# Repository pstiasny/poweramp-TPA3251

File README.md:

TPA3251-based power amplifier, 2x150W
=====================================

* [View schematic in KiCanvas](https://kicanvas.org/?github=https%3A%2F%2Fgithub.com%2Fpstiasny%2Fpoweramp-TPA3251%2Fblob%2Fmain%2Famp.kicad_sch)
* [View board in KiCanvas](https://kicanvas.org/?github=https%3A%2F%2Fgithub.com%2Fpstiasny%2Fpoweramp-TPA3251%2Fblob%2Fmain%2Famp.kicad_pcb)

## Notes

*  Amplifier chip is placed on the bottom side.  That design allows for thermal coupling to chassis.
*  I had the board bend a little.  Might be better balanced without the bottom layer ground plane.
*  DC relative to power ground will be present on the ouput terminals.  Add AC coupling capacitors
   in series if that is undesired.

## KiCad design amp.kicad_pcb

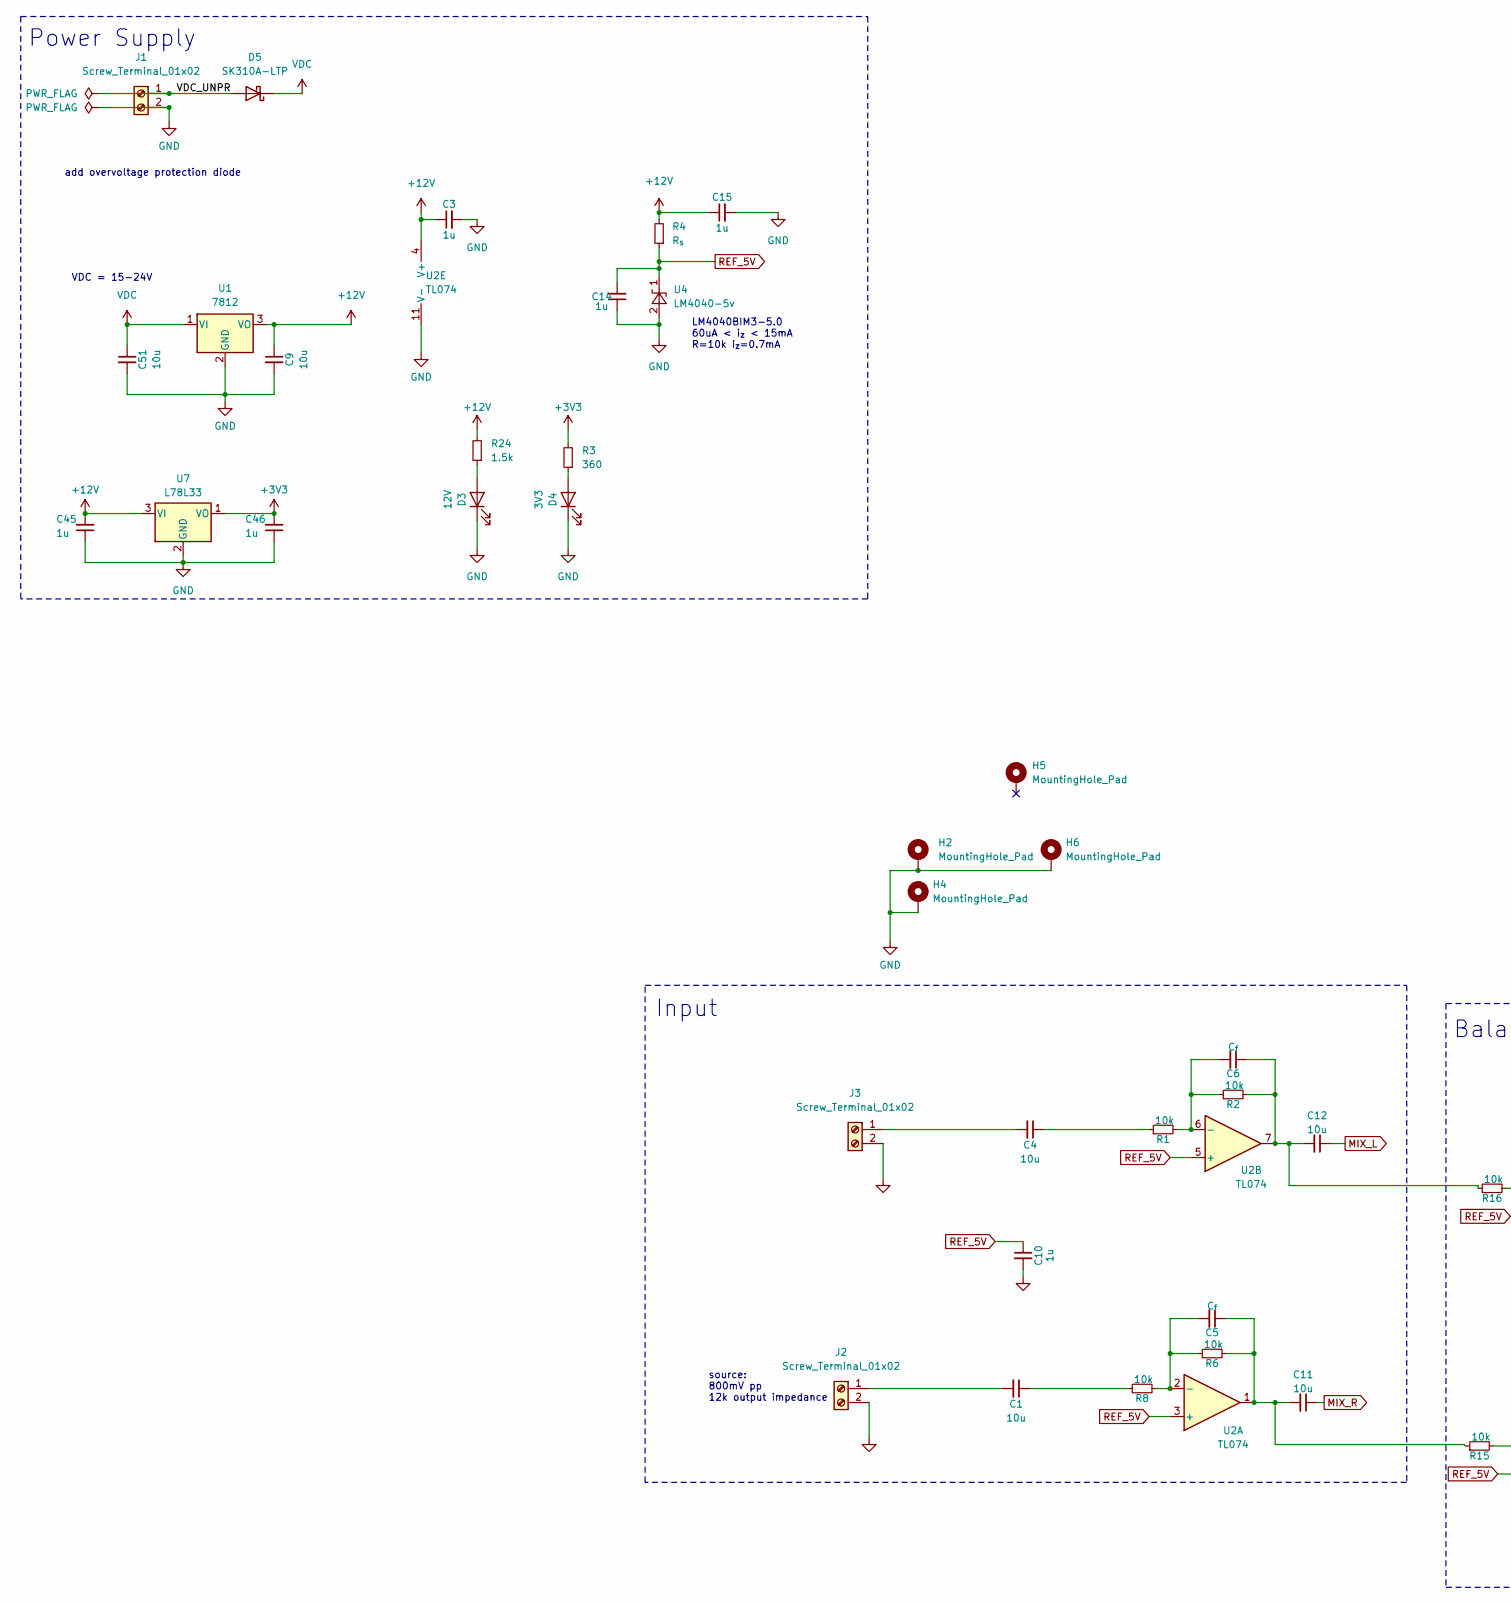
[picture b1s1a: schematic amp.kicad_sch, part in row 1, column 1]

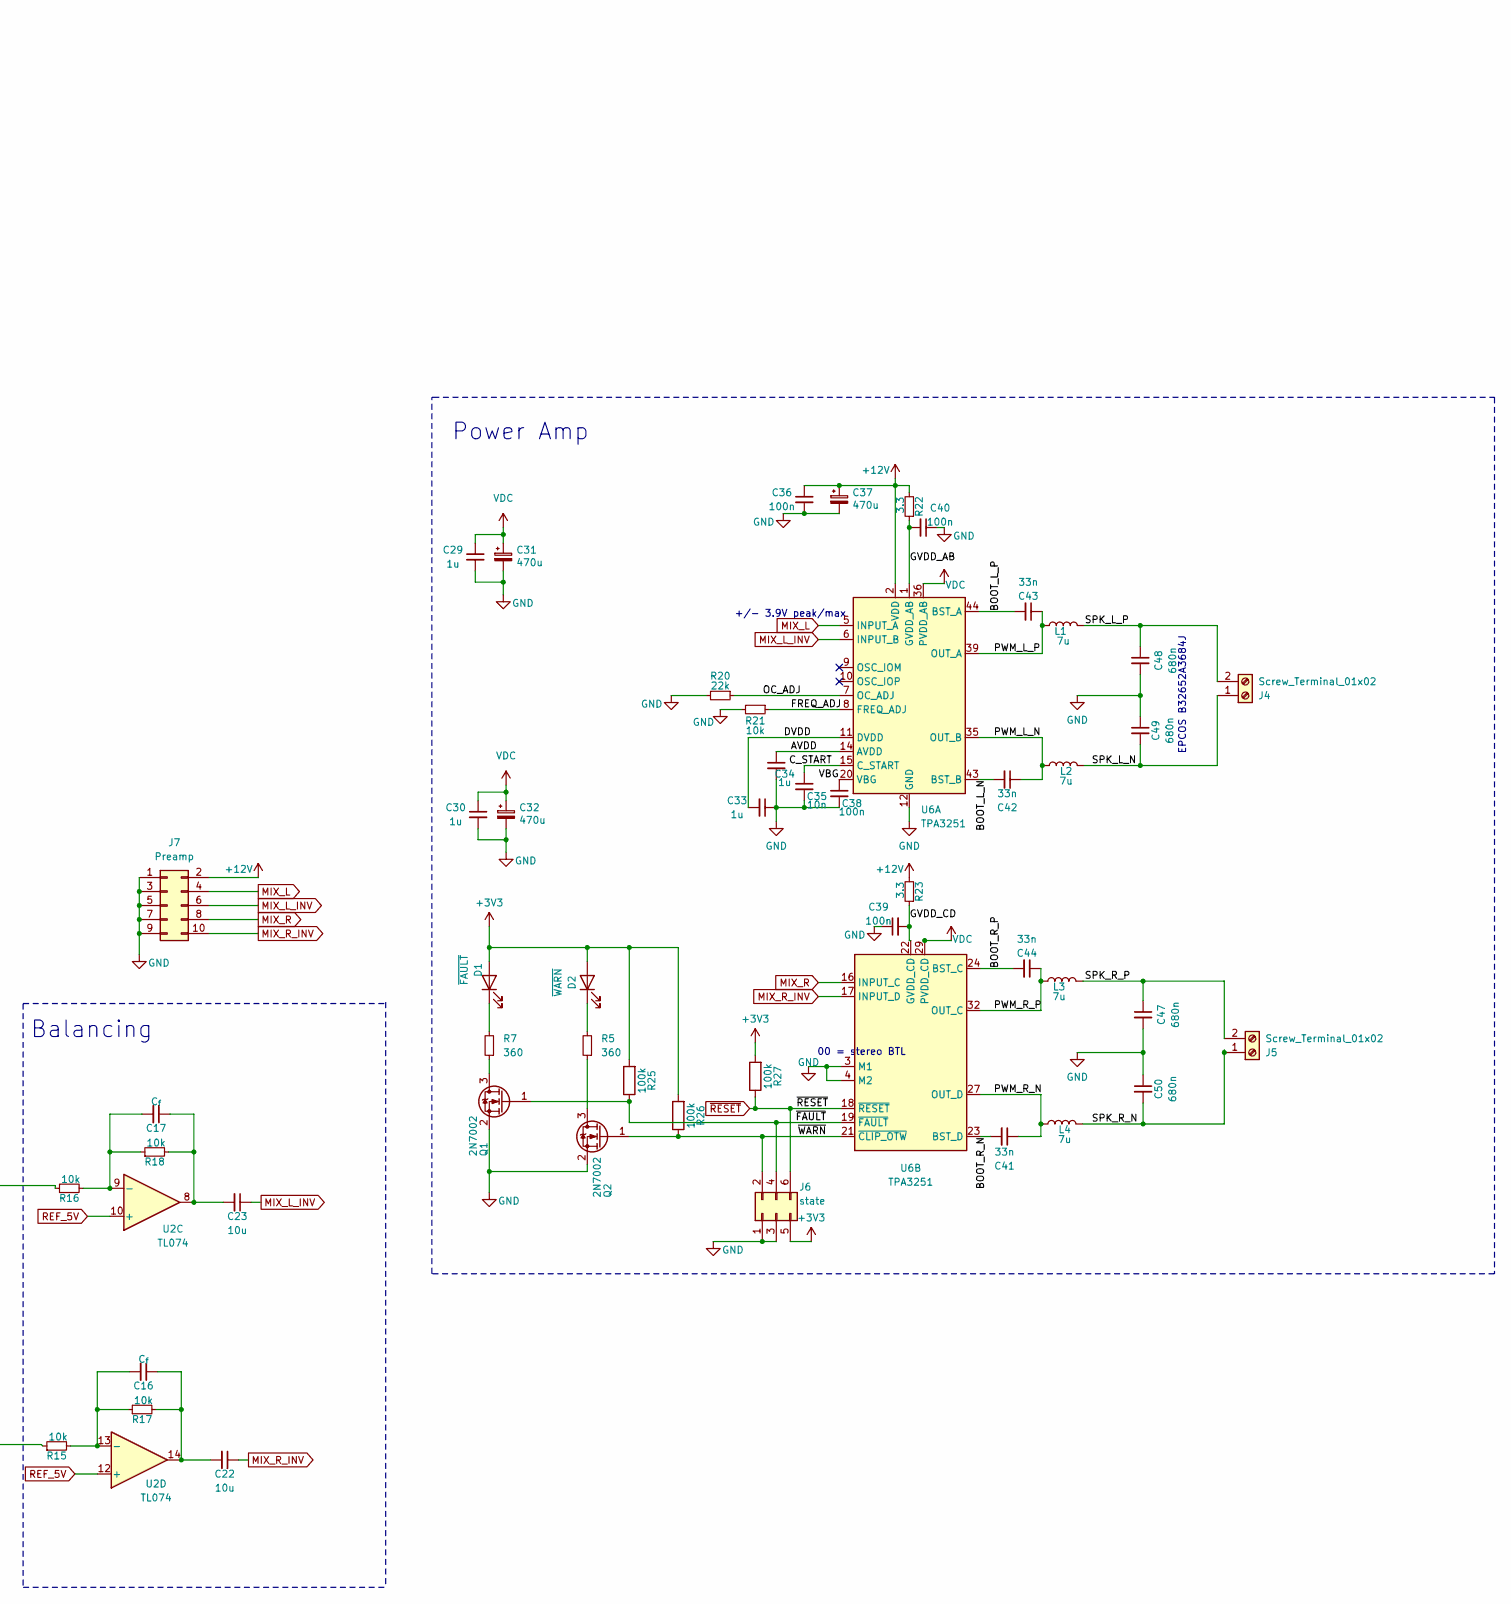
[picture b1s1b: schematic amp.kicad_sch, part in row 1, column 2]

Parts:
C1, C4, C9, C11, C12, C22, C23, C51: 10u; C_1206_3216Metric_Pad1.33x1.80mm_HandSolder
C3, C10, C14, C15, C33, C34, C45, C46: 1u; C_0805_2012Metric_Pad1.18x1.45mm_HandSolder
C5, C6, C16, C17: C_{f}; C_0805_2012Metric_Pad1.18x1.45mm_HandSolder
C29, C30: 1u; C_0402_1005Metric_Pad0.74x0.62mm_HandSolder
C31, C32, C37: 470u; CP_Radial_D12.5mm_P5.00mm
C35: 10n; C_0805_2012Metric_Pad1.18x1.45mm_HandSolder
C36, C38, C39, C40: 100n; C_0805_2012Metric_Pad1.18x1.45mm_HandSolder
C41, C42, C43, C44: 33n; C_0402_1005Metric_Pad0.74x0.62mm_HandSolder
C47, C48, C49, C50: 680n; C_Rect_L18.0mm_W9.0mm_P15.00mm_FKS3_FKP3
D1: ~{FAULT}; LED_0603_1608Metric_Pad1.05x0.95mm_HandSolder
D2: ~{WARN}; LED_0603_1608Metric_Pad1.05x0.95mm_HandSolder
D3: 12V; LED_0603_1608Metric_Pad1.05x0.95mm_HandSolder
D4: 3V3; LED_0603_1608Metric_Pad1.05x0.95mm_HandSolder
D5: SK310A-LTP; SODFL5026X125N
H2, H4, H5, H6: MountingHole_Pad; MountingHole_2.7mm_M2.5_Pad
J1, J2, J3, J4, J5: Screw_Terminal_01x02; TerminalBlock_bornier-2_P5.08mm
J6: state; PinHeader_2x03_P2.54mm_Vertical_SMD
J7: Preamp; PinHeader_2x05_P2.54mm_Vertical
L1, L2, L3, L4: 7u; WE-HCF_201322
Q1, Q2: 2N7002; SOT-23_Handsoldering
R1, R2, R6, R8, R15, R16, R17, R18, R21: 10k; R_0805_2012Metric_Pad1.20x1.40mm_HandSolder
R3, R5, R7: 360; R_0805_2012Metric_Pad1.20x1.40mm_HandSolder
R4: R_{s}; R_0805_2012Metric_Pad1.20x1.40mm_HandSolder
R20: 22k; R_0805_2012Metric_Pad1.20x1.40mm_HandSolder
R22, R23: 3.3; R_0805_2012Metric_Pad1.20x1.40mm_HandSolder
R24: 1.5k; R_0805_2012Metric_Pad1.20x1.40mm_HandSolder
R25, R26, R27: 100k; R_0805_2012Metric_Pad1.20x1.40mm_HandSolder
U1: 7812; TO-220-3_Vertical
U2: TL074; TSSOP-14_4.4x5mm_P0.65mm
U4: LM4040-5v; SOT-23
U6: TPA3251; SOP64P810X120-45N
U7: L78L33; TO-92_Inline

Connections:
+3V3: C46.2, D1.2 (A), D2.2 (A), J6.5, R3.2, R25.2, R26.2, R27.2, U7.1 (VO)
+12V: C3.1, C9.1, C15.1, C36.1, C37.1, C45.2, J7.2, R4.2, R22.2, R23.2, R24.2, U1.3 (VO), U2.4 (V+), U6.2 (VDD), U7.3 (VI)
/AVDD: C34.1, U6.14 (AVDD)
/BOOT_L_N: C42.2, U6.43 (BST_B)
/BOOT_L_P: C43.2, U6.44 (BST_A)
/BOOT_R_N: C41.2, U6.23 (BST_D)
/BOOT_R_P: C44.2, U6.24 (BST_C)
/C_START: C35.1, U6.15 (C_START)
/DVDD: C33.2, U6.11 (DVDD)
/FREQ_ADJ: R21.1, U6.8 (FREQ_ADJ)
/GVDD_AB: C40.2, R22.1, U6.1 (GVDD_AB)
/GVDD_CD: C39.2, R23.1, U6.22 (GVDD_CD)
/OC_ADJ: R20.1, U6.7 (OC_ADJ)
/PWM_L_N: C42.1, L2.1, U6.35 (OUT_B)
/PWM_L_P: C43.1, L1.2, U6.39 (OUT_A), U6.40 (OUT_A)
/PWM_R_N: C41.1, L4.1, U6.27 (OUT_D), U6.28 (OUT_D)
/PWM_R_P: C44.1, L3.2, U6.32 (OUT_C)
/SPK_L_N: C49.2, J4.1, L2.2
/SPK_L_P: C48.1, J4.2, L1.1
/SPK_R_N: C50.2, J5.1, L4.2
/SPK_R_P: C47.1, J5.2, L3.1
/VBG: C38.1, U6.20 (VBG)
/VDC_UNPR: D5.2 (A), J1.1
/~FAULT: J6.4, Q1.1 (G), R25.1, U6.19 (~FAULT)
/~WARN: J6.2, Q2.1 (G), R26.1, U6.21 (~CLIP_OTW)
GND: C3.2, C9.2, C10.2, C14.1, C15.2, C29.2, C30.2, C31.2, C32.2, C33.1, C34.2, C35.2, C36.2, C37.2, C38.2, C39.1, C40.1, C45.1, C46.1, C47.2, C48.2, C49.1, C50.1, C51.2, D3.1 (K), D4.1 (K), H2.1, H4.1, H6.1, J1.2, J2.2, J3.2, J6.1, J6.3, J7.1, J7.3, J7.5, J7.7, J7.9, Q1.2 (S), Q2.2 (S), R20.2, R21.2, U1.2 (GND), U2.11 (V-), U4.2 (A), U6.3 (M1), U6.4 (M2), U6.12 (GND), U6.13 (GND), U6.25 (GND), U6.26 (GND), U6.33 (GND), U6.34 (GND), U6.41 (GND), U6.42 (GND), U7.2 (GND)
MIX_L: C12.1, J7.4, U6.5 (INPUT_A)
MIX_L_INV: C23.1, J7.6, U6.6 (INPUT_B)
MIX_R: C11.1, J7.8, U6.16 (INPUT_C)
MIX_R_INV: C22.1, J7.10, U6.17 (INPUT_D)
unnamed: C1.1, R8.1
unnamed: C4.1, R1.1
unnamed: C5.1, C11.2, R6.2, R15.1, U2.1
unnamed: C6.1, C12.2, R2.2, R16.1, U2.7
unnamed: C16.1, C22.2, R17.2, U2.14
unnamed: C17.1, C23.2, R18.2, U2.8
unnamed: D1.1 (K), R7.2
unnamed: D2.1 (K), R5.2
unnamed: D3.2 (A), R24.1
unnamed: D4.2 (A), R3.1
unnamed: C1.2, J2.1
unnamed: C4.2, J3.1
unnamed: Q1.3 (D), R7.1
unnamed: Q2.3 (D), R5.1
unnamed: C5.2, R6.1, R8.2, U2.2 (-)
unnamed: C6.2, R1.2, R2.1, U2.6 (-)
unnamed: C17.2, R16.2, R18.1, U2.9 (-)
unnamed: C16.2, R15.2, R17.1, U2.13 (-)
REF_5V: C10.1, C14.2, R4.1, U2.3 (+), U2.5 (+), U2.10 (+), U2.12 (+), U4.1 (K)
VDC: C29.1, C30.1, C31.1, C32.1, C51.1, D5.1 (K), U1.1 (VI), U6.29 (PVDD_CD), U6.30 (PVDD_CD), U6.31 (PVDD_CD), U6.36 (PVDD_AB), U6.37 (PVDD_AB), U6.38 (PVDD_AB)
~RESET: J6.6, R27.1, U6.18 (~RESET)

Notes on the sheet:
00 = stereo BTL
Input
EPCOS B32652A3684J
source: 800mV pp 12k output impedance
Power Supply
add overvoltage protection diode
LM4040BIM3-5.0 60uA < i_{z} < 15mA R=10k i_{z}=0.7mA
Balancing
Power Amp
+/- 3.9V peak/max
VDC = 15-24V

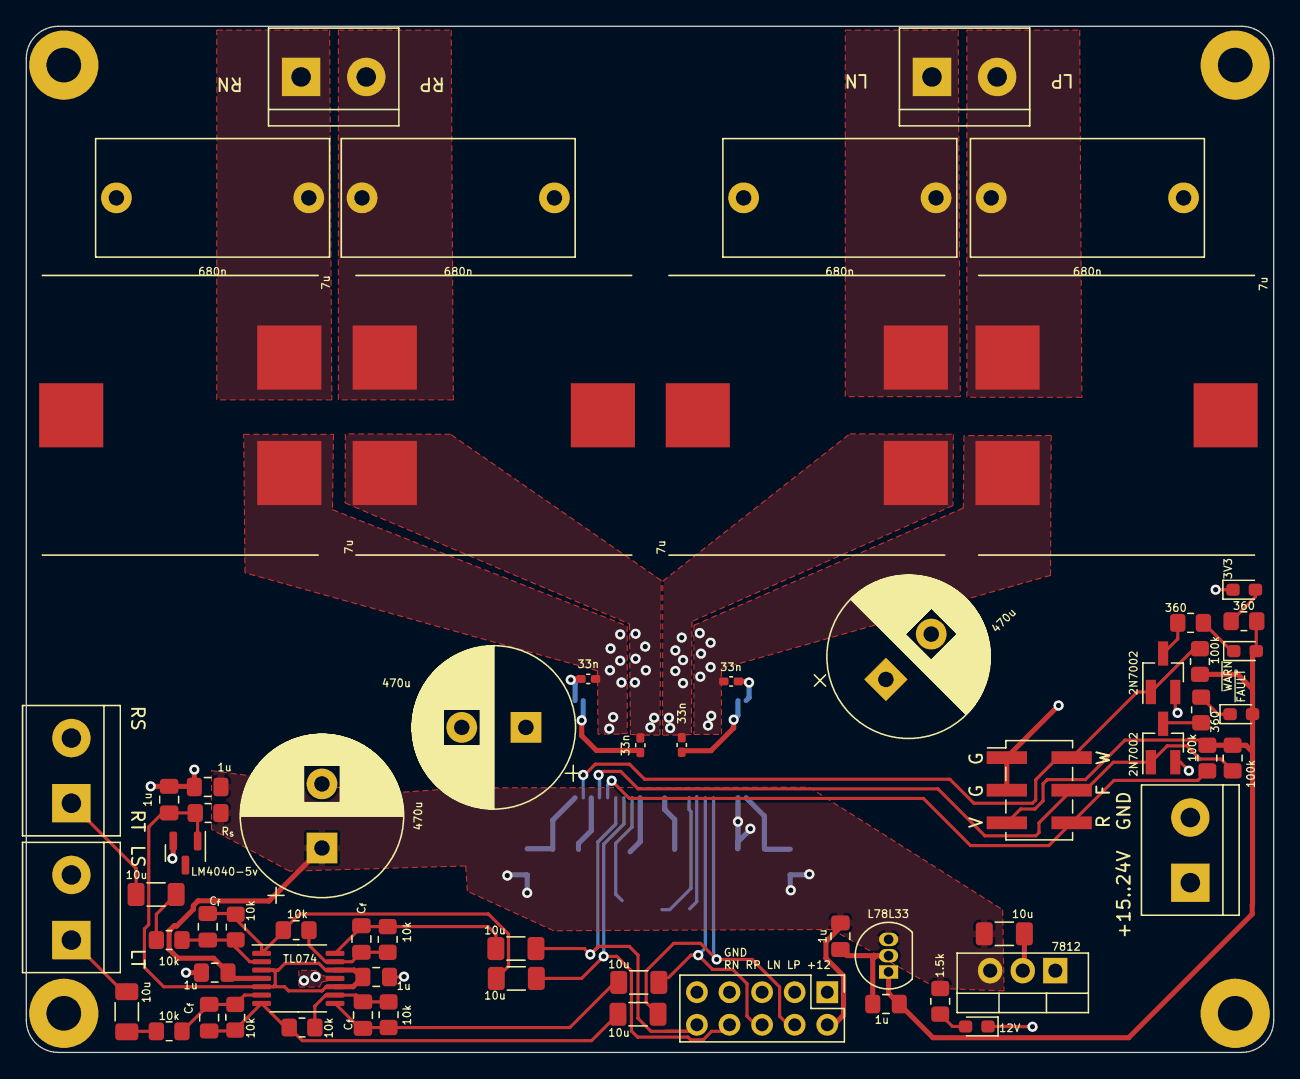
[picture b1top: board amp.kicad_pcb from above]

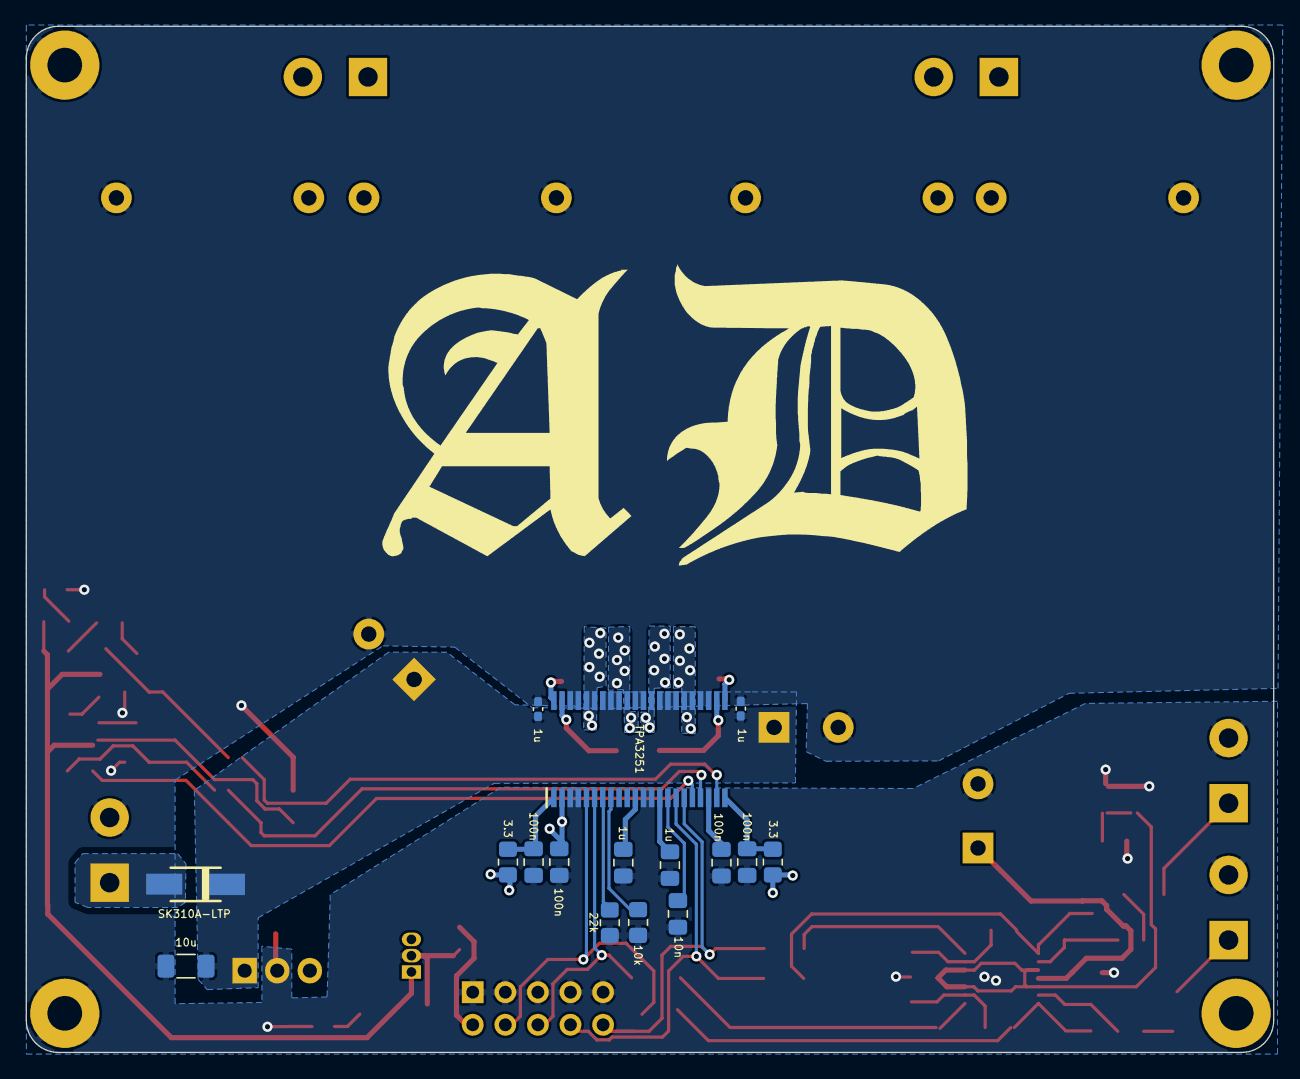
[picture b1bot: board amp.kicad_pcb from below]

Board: 4 copper layers, 97.2 x 80.0 mm, 85 parts (16 on the bottom side), 51 nets.

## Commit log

2024-09-28 add project files
2024-09-28 schematic annotations
2024-09-28 add a readme and photos
